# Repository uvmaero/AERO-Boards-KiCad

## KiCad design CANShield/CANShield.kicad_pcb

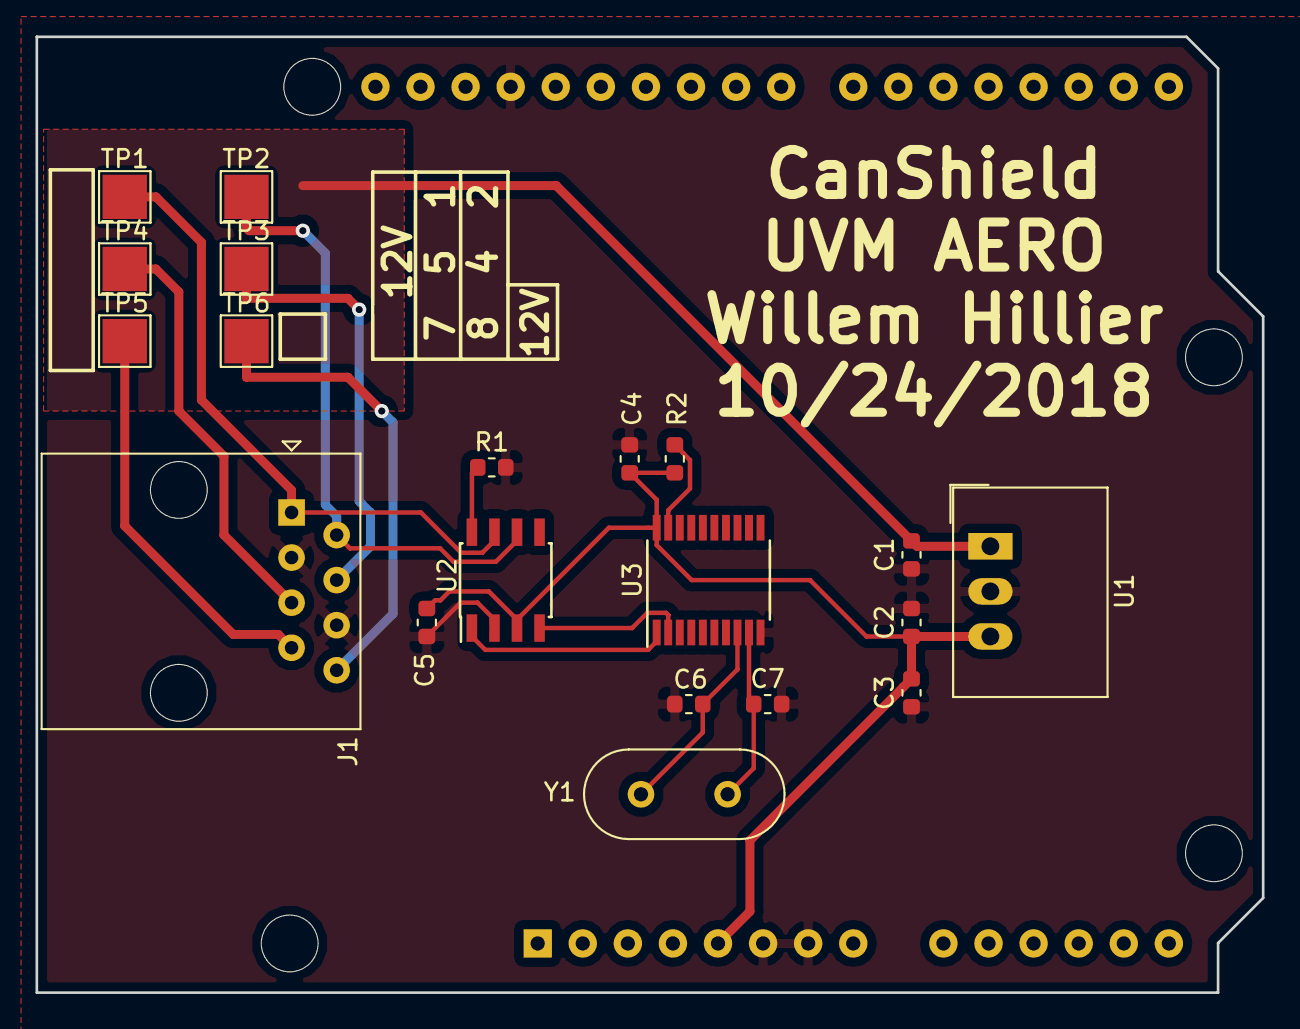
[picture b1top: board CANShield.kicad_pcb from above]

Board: 2 copper layers, 69.1 x 53.8 mm, 21 parts (1 on the bottom side), 15 nets.

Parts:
A1: Arduino_UNO_R3; Arduino_UNO_R3_WithMountingHoles
C1, C3: 10uF; C_0603_1608Metric
C2, C4, C5: 0.1uF; C_0603_1608Metric
C6, C7: 22pF; C_0603_1608Metric
J1: RJ45; RJ45_Amphenol_54602-x08_Horizontal
R1, R2: 10k; R_0603_1608Metric
TP1, TP2, TP3, TP4, TP5, TP6: TestPoint; TestPoint_Pad_2.5x2.5mm
U1: R-78E5.0-0.5; Converter_DCDC_RECOM_R-78E-0.5_THT
U2: MCP2551-I-SN; SOIC-8_3.9x4.9mm_P1.27mm
U3: MCP2515-IST; TSSOP-20_4.4x6.5mm_P0.65mm
Y1: 8MHz; Crystal_HC49-U_Vertical

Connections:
+5V: A1.5, C2.1, C3.1, C4.1, C5.1, R2.1, U1.3, U2.3, U3.20
+12V: C1.1, U1.1
GND: A1.6, A1.7, A1.29, C1.2, C2.2, C3.2, C4.2, C5.2, C6.2, C7.2, J1.3, J1.6, R1.2, U1.2, U2.2, U3.10
unnamed: C6.1, U3.8, Y1.1
unnamed: C7.1, U3.9, Y1.2
unnamed: J1.1, TP1.1, U2.7
unnamed: J1.2, TP2.1, U2.6
unnamed: J1.4, TP3.1
unnamed: J1.5, TP4.1
unnamed: J1.7, TP5.1
unnamed: J1.8, TP6.1
unnamed: R1.1, U2.8
unnamed: R2.2, U3.19
unnamed: U2.1, U3.1
unnamed: U2.4, U3.2

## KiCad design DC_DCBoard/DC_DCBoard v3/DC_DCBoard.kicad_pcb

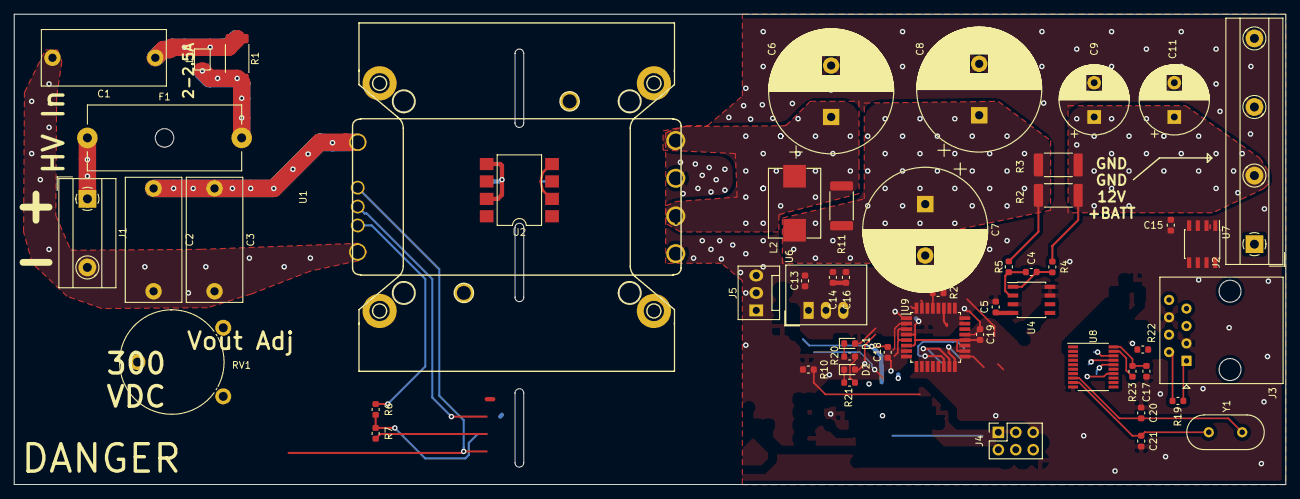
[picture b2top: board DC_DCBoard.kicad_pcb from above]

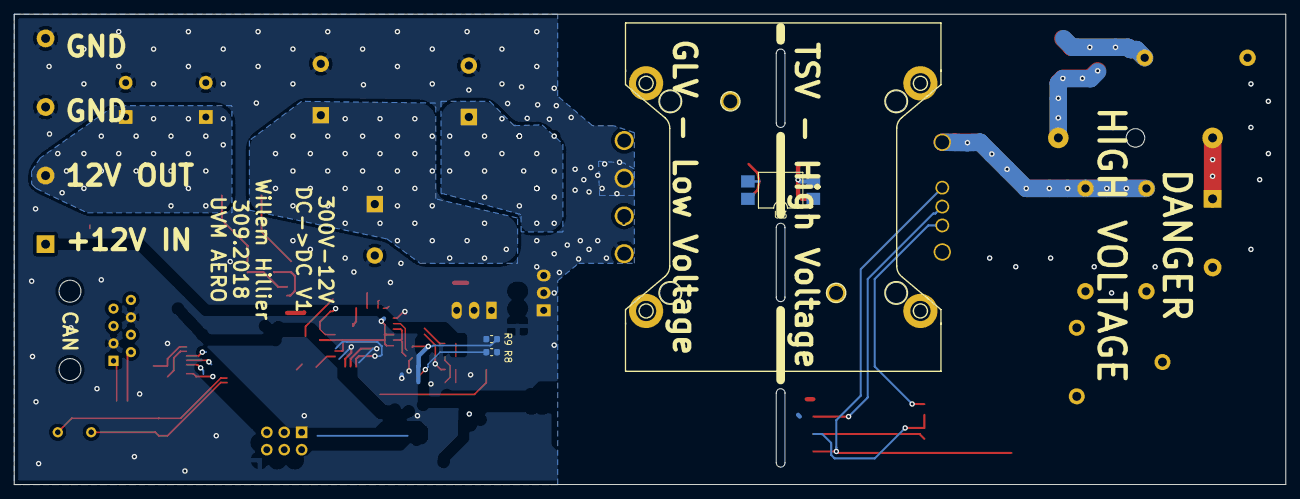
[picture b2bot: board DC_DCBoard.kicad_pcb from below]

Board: 2 copper layers, 185.4 x 68.6 mm, 56 parts (3 on the bottom side), 40 nets.

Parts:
C1, C2, C3: 0.68uF; C_Rect_L18.0mm_W8.0mm_P15.00mm_FKS3_FKP3
C4, C5, C14, C15, C17, C18, C19: 0.1uF; C_0603_1608Metric
C6, C7, C8: 4700uF; CP_Radial_D18.0mm_P7.50mm
C9, C11: 470uF; CP_Radial_D10.0mm_P5.00mm
C13, C16: 10uF; C_0603_1608Metric
C20, C21: 22pF; C_0603_1608Metric
D1, D2: LED; LED_0603_1608Metric
F1: 2.5A; Fuseholder_Cylinder-5x20mm_Schurter_0031_8201_Horizontal_Op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
J1: TSV; TerminalBlock_MetzConnect_Type067_RT01902HDWC_1x02_P10.00mm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
J2: 12V_OUT; TerminalBlock_MetzConnect_Type067_RT01904HDWC_1x04_P10.00mm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
J3: RJ45; RJ45_Amphenol_54602-x08_Horizontal
J4: Conn_02x03_Odd_Even; PinSocket_2x03_P2.54mm_Vertical
J5: FAN; FanPinHeader_1x03_P2.54mm_Vertical
L1: 1uH; Murata_DFE252012P_Inductor
L2: 0.15uH; PA2607
R1, R11: 1Ω; R_2512_6332Metric
R2, R3: 0.02; R_2512_6332Metric
R4, R5: 10; R_0603_1608Metric
R6, R8, R10, R20, R21: 1k; R_0603_1608Metric
R7: 50k; R_0603_1608Metric
R9, R22, R23, R24: 10k; R_0603_1608Metric
R19: R_US; R_0603_1608Metric
RV1: 5k; Potentiometer_Piher_PT-15-V02_Vertical
U1: DCM4623TD2J13D0T70; DCM4623TD2J13D0T70 w_landpattern
U2: LTV-827S; SMDIP-8_W9.53mm
U3: LTV-817S; SMDIP-4_W9.53mm
U4: INA219; SOIC-8_3.9x4.9mm_P1.27mm
U6: R-78E5.0-0.5; Converter_DCDC_RECOM_R-78E-0.5_THT
U7: MCP2551-I-SN; SOIC-8_3.9x4.9mm_P1.27mm
U8: MCP2515-IST; TSSOP-20_4.4x6.5mm_P0.65mm
U9: ATmega328P-AU; TQFP-32_7x7mm_P0.8mm
Y1: 16MHz; Crystal_HC49-U_Vertical

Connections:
+5V: C5.2, C14.1, C15.1, C16.1, C17.1, C18.1, C19.1, J4.2, R9.2, R23.1, R24.1, U4.4, U6.3, U7.3, U8.20, U9.4, U9.6, U9.18, U9.20
+12V: C9.1, C11.1, J2.2, R2.2, R3.2, R4.2
/12V_SAFETY_IN: C13.1, J2.1, J5.2, U6.1
/12V_UNMETERED: C7.1, C8.1, L2.2, R2.1, R3.1, R5.2, R11.1
/D10: U8.18, U9.14
/DC_DC_EN: R8.1, U9.2
/DC_DC_FAULT: R9.1, U3.4, U9.1
/EN: U1.3, U2.6
/FAULT: R6.2, U1.4
/HV+: F1.2, L1.1, R1.2
/HV-: C1.2, C2.2, C3.2, J1.2, R7.2, RV1.2, U1.5, U2.5, U2.7, U3.2
/LED1: D1.2, U9.31
/LED2: D2.2, U9.32
/MISO: J4.1, U8.17, U9.16
/MOSI: J4.4, U8.16, U9.15
/RESET: J4.5, R24.2, U9.29
/SCK: J4.3, U8.14, U9.17
/SCL: U4.5, U9.28
/SDA: U4.6, U9.27
/TRIM: RV1.3, U1.2, U2.8
/TRIM_EN: R10.1, U9.9
GND: C5.1, C6.2, C7.2, C8.2, C9.2, C11.2, C13.2, C14.2, C15.2, C16.2, C17.2, C18.2, C19.2, C20.2, C21.2, J2.3, J2.4, J3.3, J3.6, J4.6, J5.1, R20.1, R21.1, R22.2, U1.6, U1.8, U2.2, U2.4, U3.3, U4.3, U4.7, U4.8, U6.2, U7.2, U8.10, U9.3, U9.5, U9.21
unnamed: C1.1, C2.1, C3.1, L1.2, R1.1, U1.1
unnamed: C4.1, R4.1, U4.1
unnamed: C4.2, R5.1, U4.2
unnamed: C6.1, L2.1, R11.2, U1.7, U1.9
unnamed: C20.1, U8.8, Y1.1
unnamed: C21.1, U8.9, Y1.2
unnamed: D1.1, R20.2
unnamed: D2.1, R21.2
unnamed: F1.1, J1.1
unnamed: J3.1, R19.1, U7.7
unnamed: J3.2, R19.2, U7.6
unnamed: R6.1, R7.1, U3.1
unnamed: R8.2, U2.3
unnamed: R10.2, U2.1
unnamed: R22.1, U7.8
unnamed: R23.2, U8.19
unnamed: U7.1, U8.1
unnamed: U7.4, U8.2

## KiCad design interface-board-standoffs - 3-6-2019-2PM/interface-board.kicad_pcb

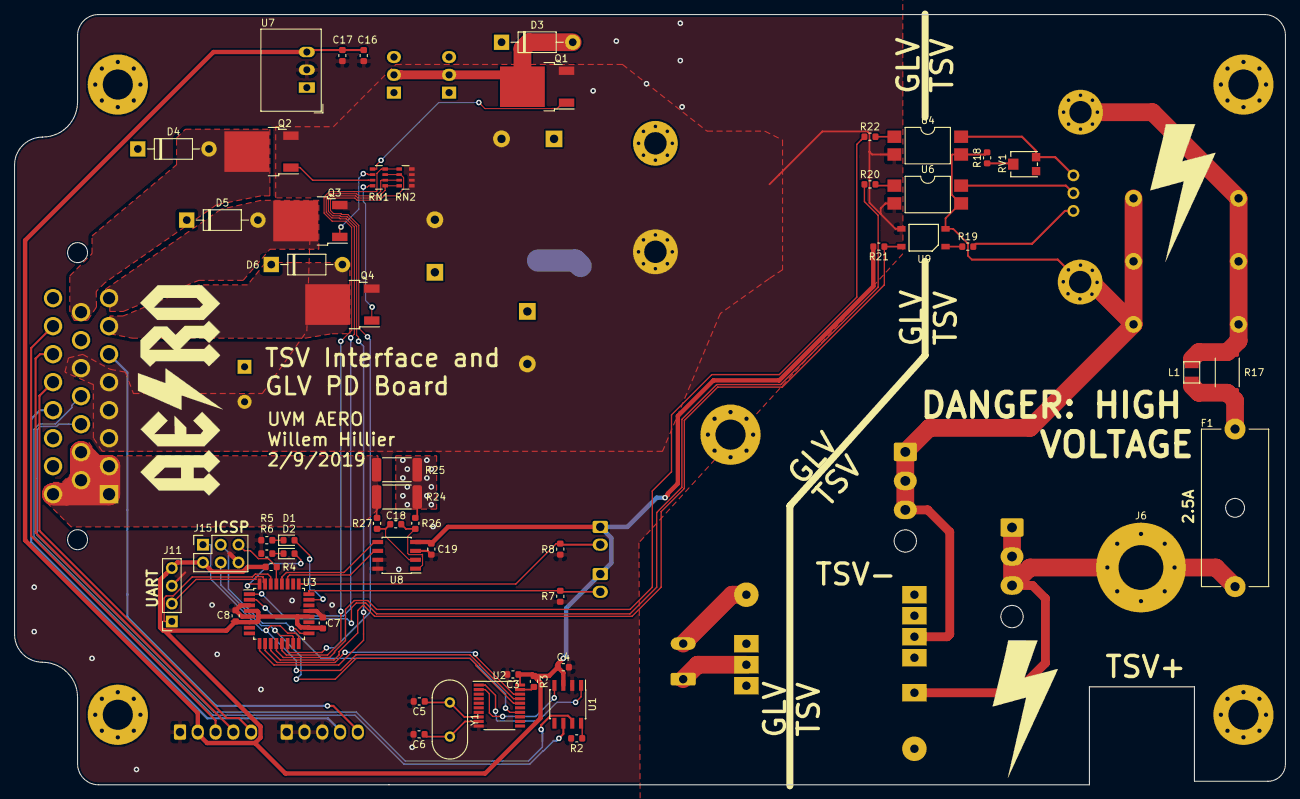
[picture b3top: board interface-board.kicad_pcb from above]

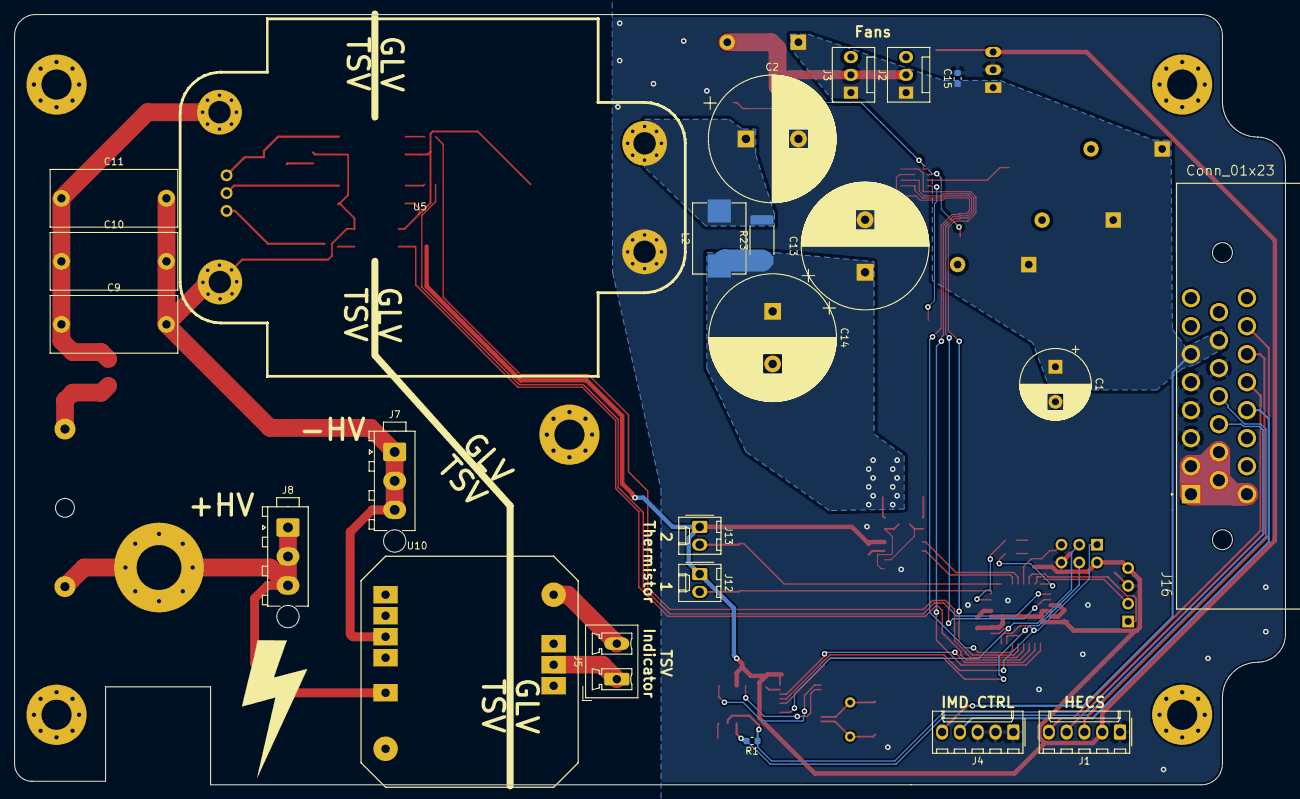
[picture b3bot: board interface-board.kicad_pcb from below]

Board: 2 copper layers, 181.5 x 110.0 mm, 77 parts (23 on the bottom side), 63 nets.

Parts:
C1: 470uF; CP_Radial_D10.0mm_P5.00mm
C2, C13, C14: 2200uF; CP_Radial_D18.0mm_P7.50mm
C3, C4, C7, C8, C16, C18, C19: 0.1uF; C_0603_1608Metric
C5, C6: 22pF; C_0603_1608Metric
C9, C10, C11: 0.68uF; C_Rect_L18.0mm_W8.0mm_P15.00mm_FKS3_FKP3
C15, C17: 10uF; C_0603_1608Metric
D1, D2: LED; LED_0603_1608Metric
D3, D4, D5, D6: 1N4001; D_DO-41_SOD81_P10.16mm_Horizontal
F1: 2A; Fuseholder_Cylinder-5x20mm_Schurter_0031_8201_Horizontal_Op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
J1: HECS; Molex_KK-254_AE-6410-05A_1x05_P2.54mm_Vertical
J2: CASEFAN1; FanPinHeader_1x03_P2.54mm_Vertical
J3: CASEFAN2; FanPinHeader_1x03_P2.54mm_Vertical
J4: Bender-LV; Molex_KK-254_AE-6410-05A_1x05_P2.54mm_Vertical
J5: BLINKY; PhoenixContact_MCV_1,5_2-G-5.08_1x02_P5.08mm_Vertical
J6: HV+; MountingHole_6.4mm_M6_Pad_Via
J7: HV-; TE_MATE-N-LOK_1-770870-x_1x03_P4.14mm_Vertical
J8: HV+; TE_MATE-N-LOK_1-770870-x_1x03_P4.14mm_Vertical
J11: UART; PinSocket_1x04_P2.54mm_Vertical
J12, J13: NTC1; Molex_KK-254_AE-6410-02A_1x02_P2.54mm_Vertical
J15: ICSP; PinSocket_2x03_P2.54mm_Vertical
J16: Conn_01x23; TE_1-776087-1
L1: 1uH; Murata_DFE252012P_Inductor
L2: 0.15uH; PA2607
Q1, Q2, Q3, Q4: Q_NMOS_GDS; TO-252-2
R1: R_US; R_0603_1608Metric
R2, R3, R4, R7, R8, R21: 10k; R_0603_1608Metric
R5, R6, R19, R20, R22: 1k; R_0603_1608Metric
R17, R23: 1Ω; R_2512_6332Metric
R18: 6.8k; R_0603_1608Metric
R24, R25: 0.02; R_2512_6332Metric
R26, R27: 10; R_0603_1608Metric
RN1: 1k; R_Array_Convex_4x0603
RN2: 10k; R_Array_Convex_4x0603
RV1: 50k; TC33X-503ECT-ND
U1: MCP2551-I-SN; SOIC-8_3.9x4.9mm_P1.27mm
U2: MCP2515-IST; TSSOP-20_4.4x6.5mm_P0.65mm
U3: ATmega328P-AU; TQFP-32_7x7mm_P0.8mm
U4, U6: LTV-817S; SMDIP-4_W9.53mm
U5: DCM4623TD2J13D0T70; vicor-socket-no-cutouts
U7: R-78E5.0-0.5; Converter_DCDC_RECOM_R-78E-0.5_THT
U8: INA219; SOIC-8_3.9x4.9mm_P1.27mm
U9: TLP184; TLP182
U10: EPM1510SJ
Y1: 16MHz; Crystal_HC49-U_Vertical

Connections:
+5V: C3.1, C4.1, C7.1, C8.1, C16.1, C17.1, C19.2, J1.2, J11.4, J12.1, J13.1, J15.2, R3.1, R4.1, R21.2, U1.3, U2.20, U3.4, U3.6, U3.18, U3.20, U7.3, U8.4
+12V: C1.1, C15.1, D3.1, D4.1, D5.1, D6.1, J2.1, J3.1, J4.5, J16.6, J16.14, U7.1
/CAN+: J16.11, R1.1, U1.7
/CAN-: J16.12, R1.2, U1.6
/DC->DC Converters/12V_OUT: C13.1, C14.1, L2.2, R23.1, R24.2, R25.2, R26.2
/DC->DC Converters/EN_HV: U5.3, U6.4
/DC->DC Converters/FAULT_HV: R19.2, U5.4
/DC->DC Converters/HV+: F1.1, L1.1, R17.2
/DC->DC Converters/TRIM_HV: RV1.3, U4.4, U5.2
/DC_DC_EN: R20.1, U3.2
/DC_DC_FAULT: R21.1, U3.11, U9.6
/DC_DC_TRIM_EN: R22.1, U3.12
/FANOUT0: D3.2, J2.2, J3.2, Q1.2
/FANOUT1: D5.2, J16.8, Q3.2
/FANOUT2: D4.2, J16.15, Q2.2
/FANOUT3: D6.2, J16.7, Q4.2
/HV+: F1.2, J6.1, J8.1, J8.2, J8.3, U10.12
/HV-: C9.2, C10.2, C11.2, J7.1, J7.2, J7.3, R18.2, U4.3, U5.5, U6.3, U9.3, U10.10
/IMD_AN1: J1.5, J16.20
/IMD_AN2: J1.4, J16.21
/IMD_AN3: J1.3, J16.22
/IMD_OK: J4.4, J16.19
/SHDN_LOOP_OUT: J16.1, J16.2, J16.9, J16.10, J16.16, R24.1, R25.1, R27.2
/TEMP_1: J12.2, R7.2, U3.24
/TEMP_2: J13.2, R8.2, U3.25
/UART_RX: J11.1, U3.30
/UART_TX: J11.2, U3.31
/fanControl/FAN_CTRL_0: RN1.4, RN2.5, U3.13
/fanControl/FAN_CTRL_1: RN1.3, RN2.6, U3.14
/fanControl/FAN_CTRL_2: RN1.2, RN2.7, U3.1
/fanControl/FAN_CTRL_3: RN1.1, RN2.8, U3.9
/uC+CAN/CAN_CS: U2.18, U3.10
/uC+CAN/LED1: D1.2, U3.23
/uC+CAN/LED2: D2.2, U3.32
/uC+CAN/MISO: J15.1, U2.17, U3.16
/uC+CAN/MOSI: J15.4, U2.16, U3.15
/uC+CAN/RESET: J15.5, R4.2, U3.29
/uC+CAN/SCK: J15.3, U2.14, U3.17
GND: C1.2, C2.2, C3.2, C4.2, C5.2, C6.2, C7.2, C8.2, C13.2, C14.2, C15.2, C16.2, C17.2, C19.1, J1.1, J4.1, J4.2, J4.3, J11.3, J15.6, J16.3, J16.4, J16.5, J16.13, Q1.3, Q2.3, Q3.3, Q4.3, R2.2, R5.1, R6.1, R7.1, R8.1, RN2.1, RN2.2, RN2.3, RN2.4, U1.2, U2.10, U3.3, U3.5, U3.21, U4.2, U5.8, U6.2, U7.2, U8.3, U8.7, U8.8, U9.4
unnamed: C5.1, U2.8, Y1.1
unnamed: C6.1, U2.9, Y1.2
unnamed: C9.1, C10.1, C11.1, L1.2, R17.1, U5.1
unnamed: C2.1, L2.1, R23.2, U5.9
unnamed: C18.1, R26.1, U8.1
unnamed: C18.2, R27.1, U8.2
unnamed: D1.1, R5.2
unnamed: D2.1, R6.2
unnamed: J5.1, U10.5
unnamed: J5.2, U10.7
unnamed: Q1.1, RN1.5
unnamed: Q2.1, RN1.7
unnamed: Q3.1, RN1.6
unnamed: Q4.1, RN1.8
unnamed: R2.1, U1.8
unnamed: R3.2, U2.19
unnamed: R18.1, RV1.2
unnamed: R19.1, U9.1
unnamed: R20.2, U6.1
unnamed: R22.2, U4.1
unnamed: U1.1, U2.1
unnamed: U1.4, U2.2
SCL: U3.28, U8.5
SDA: U3.27, U8.6
